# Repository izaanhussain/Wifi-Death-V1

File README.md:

# WiFi Death V1

> A custom ESP32-C3 WiFi testing/hacking device with a 0.96" OLED display and four physical controls.

## Required Library Setup

Open Arduino IDE
Install OLED libraries: Tools -> Manage Libraries -> search Adafruit SSD1306 -> install
fig1

Add esp32 additional board manager URL: Files -> Preferences -> add https://raw.githubusercontent.com/espressif/arduino-esp32/gh-pages/package_esp32_dev_index.json to Additional Boards Manager URLs

Install esp32 board manager: Tools -> Board -> Boards Manager -> search esp32 -> install esp32 by Espressif Systems

## Firmware Installation 

1. Clone the repo or Download raw .zip file
2. open Arduino IDE
3. open Wifi_Death_v1.ino
4. upload to your device

---

## What is this?

WiFi Death V1 is a custom ESP32-C3 based wifi hacking/testing hardware project that I designed , The idea started when i saw a video of spacehunns esp8266 deauther and i knew i wanted to make this but with different board like the c3.

## Key Features
- WiFi Scanning: The project can scan for available WiFi networks in the vicinity and display information about them, such as their name, signal strength, and channel.
  
- Deauthentication Attacks: With the push of a button, the project can perform deauthentication attacks on specific networks or clients, making it useful for penetration testing and network security auditing.
  
- 0.96-inch OLED Display: The project uses a small OLED display to show information about the networks in real-time.
  
- Circuit Design: The project's circuit is relatively simple and only requires connecting the ESP32 board to the OLED display.
  
---

## Hardware

The current PCB uses:

| Component | Quantity |
|---|---:|
| ESP32-C3 SuperMini | 1 |
| 0.96" 128×64 I2C OLED | 1 |
| 6×6×5 mm tactile buttons | 4 |
| Custom PCB | 1 |

### Controls

The four buttons are:

- **UP**
- **DOWN**
- **SELECT**
- **BACK**

The OLED is used as the main display.

---

## Display

The project uses a:

**0.96" 128×64 SSD1306 I2C OLED**

The OLED is connected directly to the ESP32-C3.

---

## ESP32-C3 Pinout

| Function | ESP32-C3 GPIO |
|---|---:|
| OLED SDA | GPIO6 |
| OLED SCL | GPIO7 |
| UP | GPIO3 |
| DOWN | GPIO4 |
| BACK | GPIO2 |
| SELECT | GPIO1 |

The board is powered through the **USB-C connector on the ESP32-C3 SuperMini**.

---

## PCB

The PCB was designed in **KiCad**.

The repository contains:

- KiCad schematic
- KiCad PCB layout
- Gerber files
- Drill files
- BOM
- PCB production files

The PCB uses a **black solder mask** so it looks cool and has **"WIFI DEATH V1"** on the front silkscreen. I also added the GitHub repo link in the backside of the pcb

---

## 📁 Repository Structure

```text
Wifi-Death-V1/
│
├── Firmware/
│   └── Firmware source
│
├── Images/
│   └── Project photos and renders
│
├── PCB/
│   ├── KiCad project
│   ├── Schematic
│   ├── PCB layout
│   └── BOM
│
├── Production/
│   └── Gerber and drill files
│
└── README.md

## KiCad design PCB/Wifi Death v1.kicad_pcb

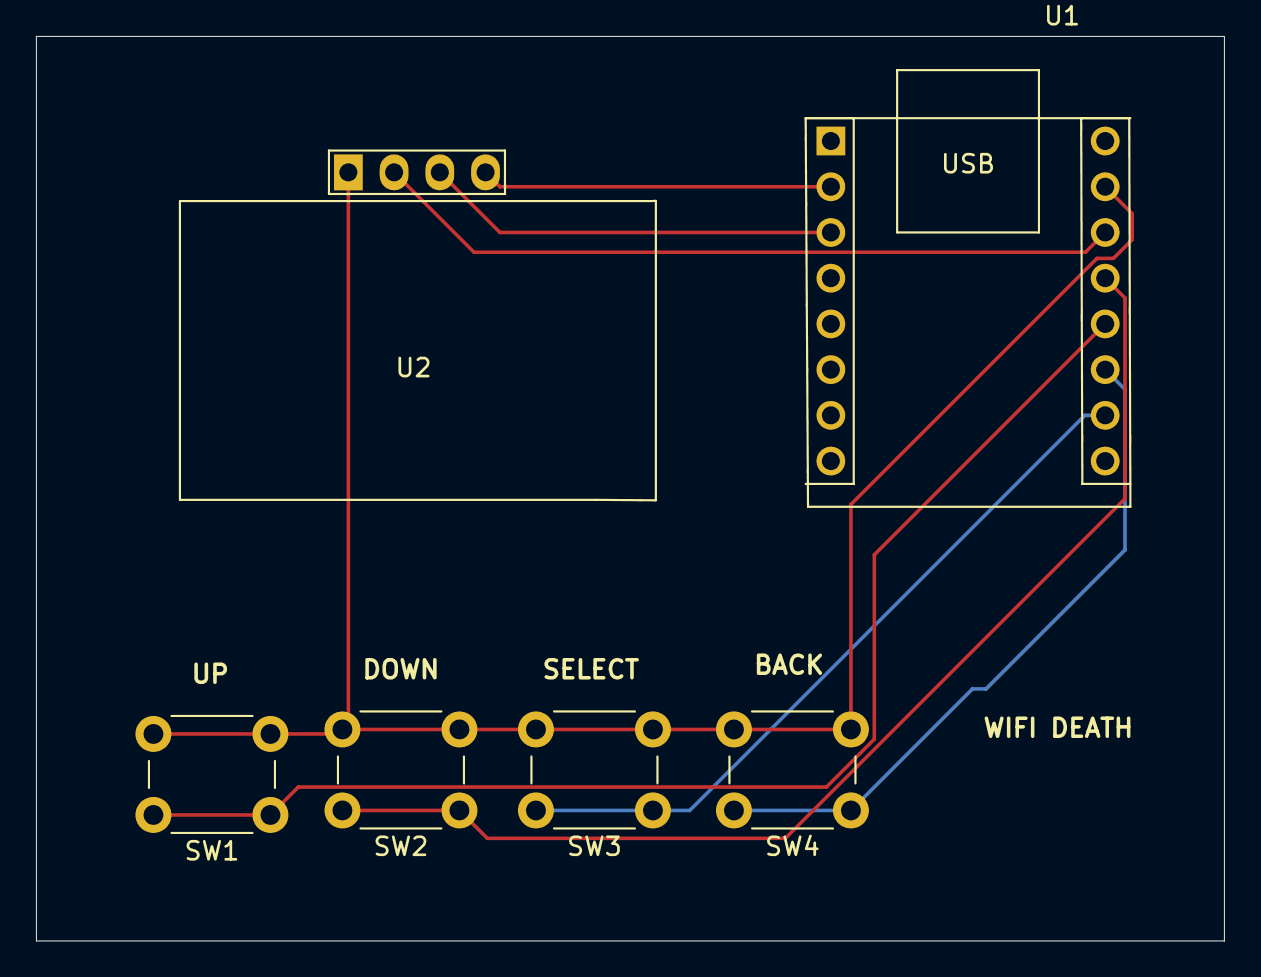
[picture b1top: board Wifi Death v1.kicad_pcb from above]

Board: 2 copper layers, 66.0 x 50.2 mm, 6 parts (0 on the bottom side), 8 nets.

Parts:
SW1, SW2, SW3, SW4: SW_Push_Dual; SW_PUSH_6mm_H5mm
U1: ESP32_C3_Super_Mini
U2: ER_OLEDM0.91_1x-I2C; 128x64OLED

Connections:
/BACK: SW4.1, U1.2 (GPIO2)
/DOWN: SW2.1, U1.4 (GPIO4)
/SCL: U1.7 (GPIO7), U2.3 (SCL)
/SDA: U1.6 (GPIO6), U2.4 (SDA)
/SELECT: SW3.1, U1.1 (GPIO1)
/UP: SW1.1, U1.3 (GPIO3)
GND: SW1.2, SW2.2, SW3.2, SW4.2, U1.-2 (GND), U2.1 (GND)
unnamed: U1.-3 (3.3V), U2.2 (VCC)
